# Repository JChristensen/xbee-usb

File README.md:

# XBee USB Dongle
https://github.com/JChristensen/xbee-usb  
README file  
Jack Christensen Feb-2018

## Overview
This dongle was mainly intended to connect an XBee semi-permanently to a Raspberry Pi, neatly without cables, for communication with an application program. Of course it can be used with any other computer as well. It's also useful for programming an XBee with [Digi's XCTU utility](https://www.digi.com/products/xbee-rf-solutions/xctu-software/xctu), or as a range extender in the mesh network by just plugging it into a 5V wall wart, phone charger, etc.

Via a solder jumper on the back of the board, the XBee's reset pin can be connected either to a pushbutton switch or to the CBUS3 pin on the FTDI FT231X chip. To use CBUS3 as a reset line, configure it as a GPIO pin using [the FTDI FT_PROG utility](http://www.ftdichip.com/Support/Utilities.htm#FT_PROG).

PC boards can be ordered [from OSH Park](https://www.oshpark.com/shared_projects/egIOkt1Z).  
A bill of materials is available [at Mouser Electronics](https://www.mouser.com/ProjectManager/ProjectDetail.aspx?AccessID=f236469f0d) and also in this repo.

**Raspberry Pi Zero with [Zero4U USB hub](https://www.adafruit.com/product/3298) and XBee USB Dongle.**

## CC BY-SA
"XBee USB Dongle" by Jack Christensen is licensed under [CC BY-SA 4.0](https://creativecommons.org/licenses/by-sa/4.0/).

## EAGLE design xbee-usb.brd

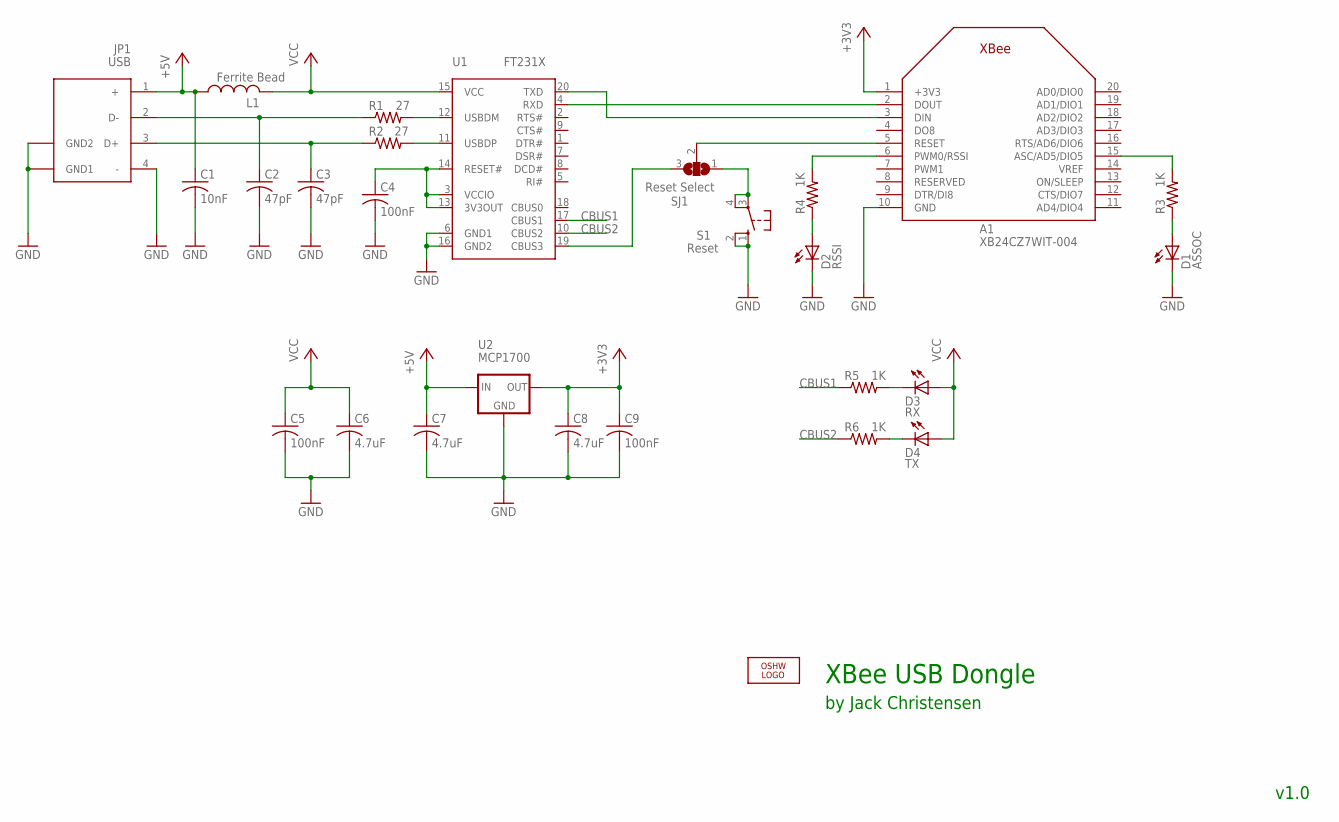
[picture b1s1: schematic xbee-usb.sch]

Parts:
A1: XB24CZ7WIT-004; XBEE_OVAL_PADS
C1: 10nF; M0805
C2, C3: 47pF; M0805
C4, C5, C9: 100nF; M0805
C6, C7, C8: 4.7uF; M0805
D1: ASSOC; D0805
D2: RSSI; D0805A
D3: RX; D0805
D4: TX; D0805A
JP1: USB; UP2-AH-X-TH
L1: Ferrite Bead; M0805
LOGO1: OSHW_LOGO_8MILX0100-NT; OSHW_8X100_NOTEXT
R1, R2: 27; M0805
R3, R4, R5, R6: 1K; M0805
S1: Reset; B3F-10XXOCT
SJ1: Reset Select; SJ_2
U1: FT231X; SSOP20-W
U2: MCP1700; SOT23-W

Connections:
+3V3: A1.1 (+3V3), C8.1, C9.1, U2.2 (OUT)
+5V: C1.1, C7.1, JP1.1 (+), L1.1, U2.3 (IN)
CBUS1: R5.1, U1.17 (CBUS1)
CBUS2: R6.1, U1.10 (CBUS2)
GND: A1.10 (GND), C1.2, C2.2, C3.2, C4.2, C5.2, C6.2, C7.2, C8.2, C9.2, D1.K (C), D2.K (C), JP1.4 (-), JP1.P$5 (GND1), JP1.P$6 (GND2), S1.1 (S), S1.2 (S1), U1.6 (GND1), U1.16 (GND2), U2.1 (GND)
unnamed: C2.1, JP1.2 (D-), R1.1
unnamed: C3.1, JP1.3 (D+), R2.1
unnamed: C4.1, U1.3 (VCCIO), U1.13 (3V3OUT), U1.14 (RESET#)
unnamed: R1.2, U1.12 (USBDM)
unnamed: R2.2, U1.11 (USBDP)
unnamed: A1.2 (DOUT), U1.4 (RXD)
unnamed: A1.3 (DIN), U1.20 (TXD)
unnamed: D3.K (C), R5.2
unnamed: A1.5 (RESET), SJ1.2
unnamed: D2.A, R4.1
unnamed: D1.A, R3.1
unnamed: A1.6 (PWM0/RSSI), R4.2
unnamed: A1.15 (ASC/AD5/DIO5), R3.2
unnamed: D4.K (C), R6.2
unnamed: S1.3, S1.4 (P1), SJ1.1
unnamed: SJ1.3, U1.19 (CBUS3)
VCC: C5.1, C6.1, D3.A, D4.A, L1.2, U1.15 (VCC)

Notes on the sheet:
XBee USB Dongle
by Jack Christensen
v1.0

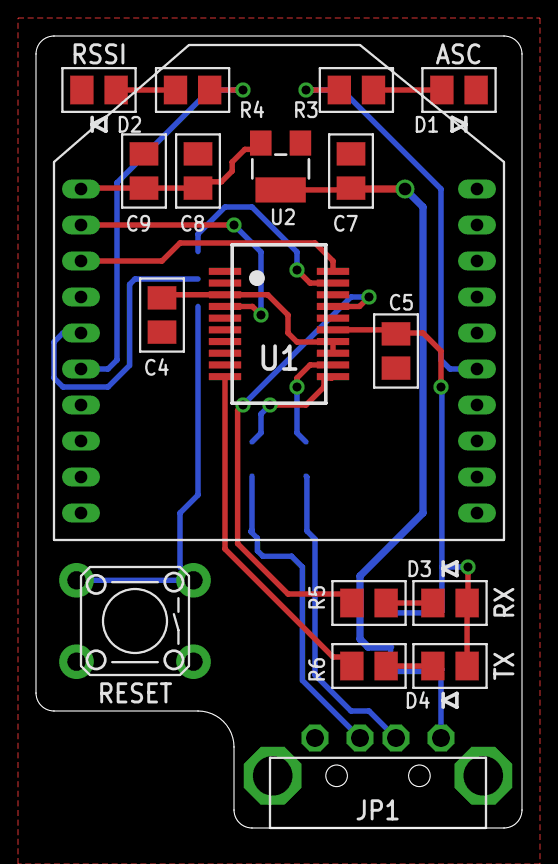
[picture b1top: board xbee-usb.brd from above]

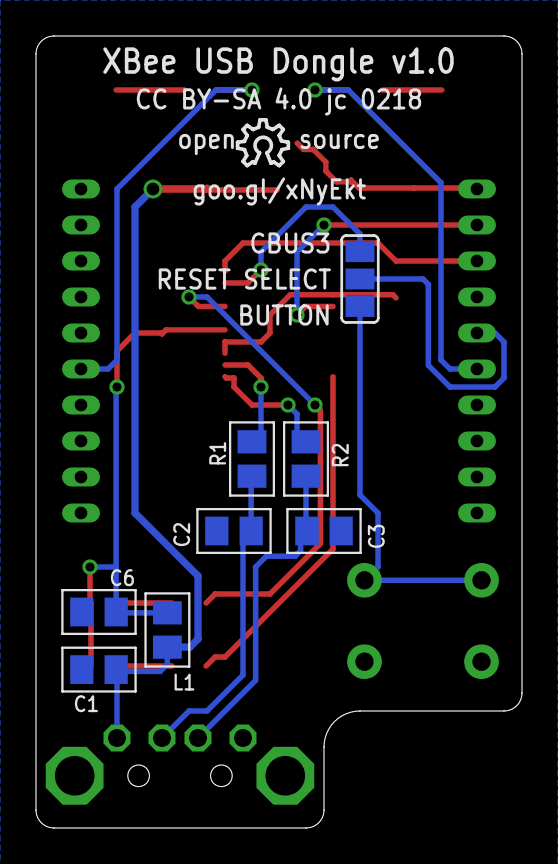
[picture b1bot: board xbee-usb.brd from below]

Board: 2 copper layers, 27.0 x 44.0 mm, 27 parts (9 on the bottom side), 22 nets.

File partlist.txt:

Partlist

Exported from xbee-usb.sch at 2/15/2018 2:13 PM

EAGLE Version 7.5.0 Copyright (c) 1988-2015 CadSoft

Assembly variant: 

Part     Value          Device             Package        Library  Sheet

A1       XB24CZ7WIT-004 ULINK_XBEEOVALPADS XBEE_OVAL_PADS _jc      1
C1       10nF           C-USM0805          M0805          _jc      1
C2       47pF           C-USM0805          M0805          _jc      1
C3       47pF           C-USM0805          M0805          _jc      1
C4       100nF          C-USM0805          M0805          _jc      1
C5       100nF          C-USM0805          M0805          _jc      1
C6       4.7uF          C-USM0805          M0805          _jc      1
C7       4.7uF          C-USM0805          M0805          _jc      1
C8       4.7uF          C-USM0805          M0805          _jc      1
C9       100nF          C-USM0805          M0805          _jc      1
D1       ASSOC          LEDD0805           D0805          _jc      1
D2       RSSI           LEDD0805A          D0805A         _jc      1
D3       RX             LEDD0805           D0805          _jc      1
D4       TX             LEDD0805A          D0805A         _jc      1
JP1      USB            UP2-AH-TH          UP2-AH-X-TH    _jc      1
L1       Ferrite Bead   INDUCTORM0805      M0805          _jc      1
R1       27             R-US_M0805         M0805          _jc      1
R2       27             R-US_M0805         M0805          _jc      1
R3       1K             R-US_M0805         M0805          _jc      1
R4       1K             R-US_M0805         M0805          _jc      1
R5       1K             R-US_M0805         M0805          _jc      1
R6       1K             R-US_M0805         M0805          _jc      1
S1       Reset          10-XXOCT           B3F-10XXOCT    _jc      1
SJ1      Reset Select   SJ2W               SJ_2           jumper   1
U1       FT231X         FT231XSSOP20-W     SSOP20-W       _jc      1
U2       MCP1700        MCP1700SOT23-W     SOT23-W        _jc      1

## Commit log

2018-02-09 Initial commit.
2018-02-15 As sent to fab.
2018-03-09 Add photos, doc, BOM, etc.

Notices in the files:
xbee-usb.brd:
CC BY-SA 4.0 jc 0218
